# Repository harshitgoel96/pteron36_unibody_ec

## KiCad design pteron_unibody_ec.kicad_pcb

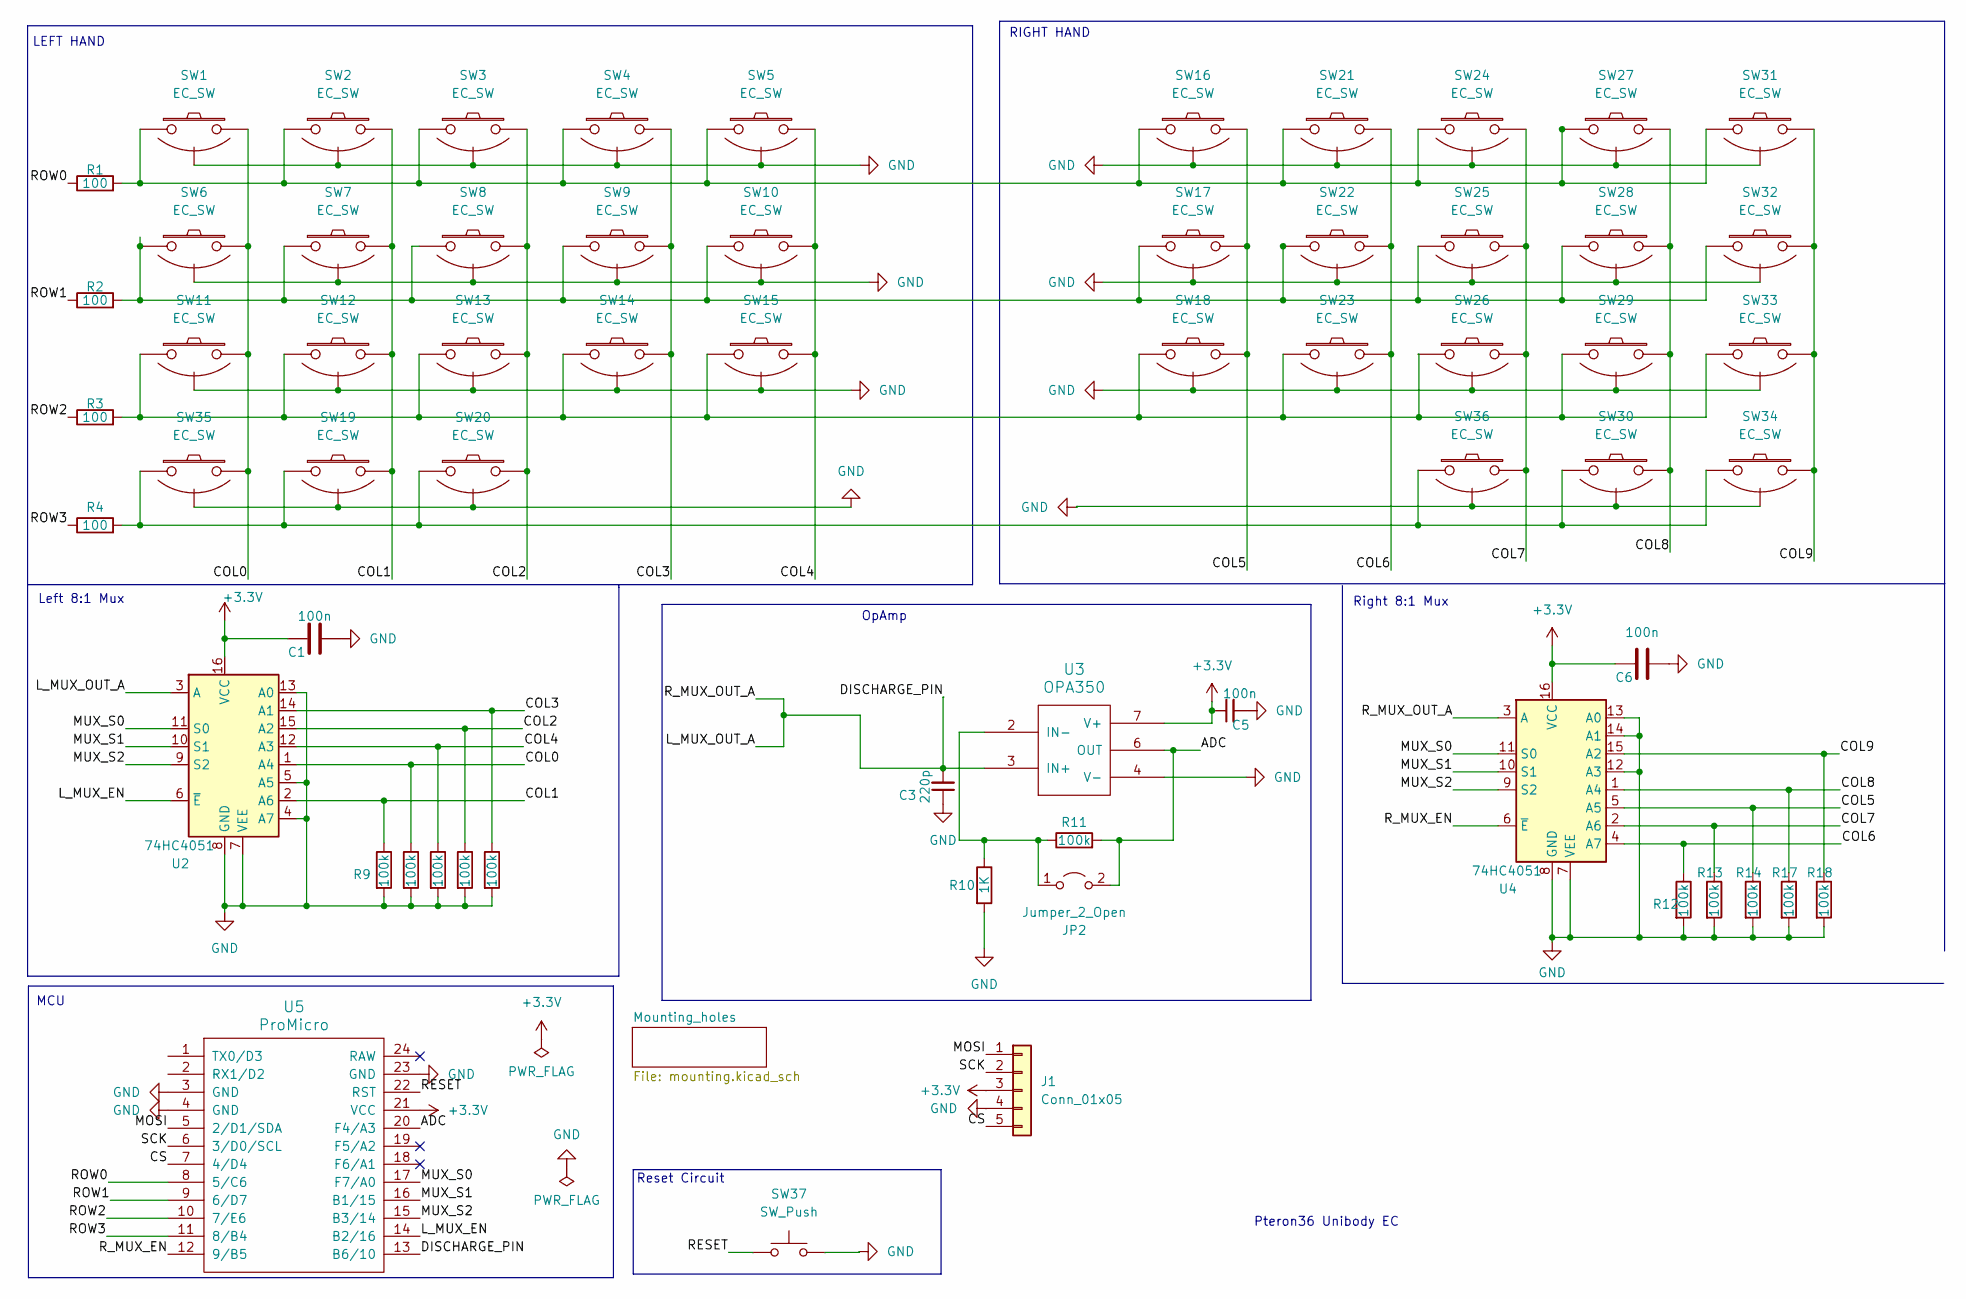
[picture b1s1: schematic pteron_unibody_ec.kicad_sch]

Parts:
C1, C5, C6: 100n; C_0805_2012Metric_Pad1.18x1.45mm_HandSolder
C3: 220p; C_0805_2012Metric_Pad1.18x1.45mm_HandSolder
J1: Conn_01x05; nice_view
JP2: Jumper_2_Open; R_0805_2012Metric_Pad1.20x1.40mm_HandSolder
R1, R2, R3, R4: 100; R_0805_2012Metric_Pad1.20x1.40mm_HandSolder
R5, R6, R7, R8, R9, R11, R12, R13, R14, R17, R18: 100k; R_0805_2012Metric_Pad1.20x1.40mm_HandSolder
R10: 1K; R_0805_2012Metric_Pad1.20x1.40mm_HandSolder
SW1, SW2, SW3, SW4, SW5, SW6, SW7, SW8, SW9, SW10, SW11, SW12, SW13, SW14, SW15, SW16, SW17, SW18, SW21, SW22, SW23, SW24, SW25, SW26, SW27, SW28, SW29, SW31, SW32, SW33: EC_SW; ecs_pad_1U_no_ring_90_fix
SW19, SW20, SW30, SW34, SW35, SW36: EC_SW; ecs_pad_1U_no_ring_90deg
SW37: SW_Push; SolderJumper-2_P1.3mm_Open_Pad1.0x1.5mm
U2, U4: 74HC4051; SOIC-16_3.9x9.9mm_P1.27mm
U3: OPA350; SOIC-8_3.9x4.9mm_P1.27mm
U5: ProMicro; ArduinoProMicro

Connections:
+3.3V: C1.1, C5.1, C6.1, J1.3, U2.16 (VCC), U3.7 (V+), U4.16 (VCC), U5.21 (VCC)
/ADC: JP2.2 (B), R11.2, U3.6 (OUT), U5.20 (F4/A3)
/COL0: R8.1, SW1.2, SW6.2, SW11.2, SW35.2, U2.1 (A4)
/COL1: R9.1, SW2.2, SW7.2, SW12.2, SW19.2, U2.2 (A6)
/COL2: R6.1, SW3.2, SW8.2, SW13.2, SW20.2, U2.15 (A2)
/COL3: R5.1, SW4.2, SW9.2, SW14.2, U2.14 (A1)
/COL4: R7.1, SW5.2, SW10.2, SW15.2, U2.12 (A3)
/COL5: R14.1, SW16.2, SW17.2, SW18.2, U4.5 (A5)
/COL6: R12.1, SW21.2, SW22.2, SW23.2, U4.4 (A7)
/COL7: R13.1, SW24.2, SW25.2, SW26.2, SW36.2, U4.2 (A6)
/COL8: R17.1, SW27.2, SW28.2, SW29.2, SW30.2, U4.1 (A4)
/COL9: R18.1, SW31.2, SW32.2, SW33.2, SW34.2, U4.15 (A2)
/CS: J1.5, U5.7 (4/D4)
/DISCHARGE_PIN: C3.2, U2.3 (A), U3.3 (IN+), U4.3 (A), U5.13 (B6/10)
/L_MUX_EN: U2.6 (~E), U5.14 (B2/16)
/MOSI: J1.1, U5.5 (2/D1/SDA)
/MUX_S0: U2.11 (S0), U4.11 (S0), U5.17 (F7/A0)
/MUX_S1: U2.10 (S1), U4.10 (S1), U5.16 (B1/15)
/MUX_S2: U2.9 (S2), U4.9 (S2), U5.15 (B3/14)
/RESET: SW37.1, U5.22 (RST)
/ROW0: R1.1, U5.8 (5/C6)
/ROW1: R2.1, U5.9 (6/D7)
/ROW2: R3.1, U5.10 (7/E6)
/ROW3: R4.1, U5.11 (8/B4)
/R_MUX_EN: U4.6 (~E), U5.12 (9/B5)
/SCK: J1.2, U5.6 (3/D0/SCL)
GND: C1.2, C3.1, C5.2, C6.2, J1.4, R5.2, R6.2, R7.2, R8.2, R9.2, R10.2, R12.2, R13.2, R14.2, R17.2, R18.2, SW1.3 (SG), SW2.3 (SG), SW3.3 (SG), SW4.3 (SG), SW5.3 (SG), SW6.3 (SG), SW7.3 (SG), SW8.3 (SG), SW9.3 (SG), SW10.3 (SG), SW11.3 (SG), SW12.3 (SG), SW13.3 (SG), SW14.3 (SG), SW15.3 (SG), SW16.3 (SG), SW17.3 (SG), SW18.3 (SG), SW19.3 (SG), SW20.3 (SG), SW21.3 (SG), SW22.3 (SG), SW23.3 (SG), SW24.3 (SG), SW25.3 (SG), SW26.3 (SG), SW27.3 (SG), SW28.3 (SG), SW29.3 (SG), SW30.3 (SG), SW31.3 (SG), SW32.3 (SG), SW33.3 (SG), SW34.3 (SG), SW35.3 (SG), SW36.3 (SG), SW37.2, U2.4 (A7), U2.5 (A5), U2.7 (VEE), U2.8 (GND), U2.13 (A0), U3.4 (V-), U4.7 (VEE), U4.8 (GND), U4.12 (A3), U4.13 (A0), U4.14 (A1), U5.3 (GND), U5.4 (GND), U5.23 (GND)
unnamed: JP2.1 (A), R10.1, R11.1, U3.2 (IN-)
unnamed: R1.2, SW1.1, SW2.1, SW3.1, SW4.1, SW5.1, SW16.1, SW21.1, SW24.1, SW27.1, SW31.1
unnamed: R2.2, SW6.1, SW7.1, SW8.1, SW9.1, SW10.1, SW17.1, SW22.1, SW25.1, SW28.1, SW32.1
unnamed: R3.2, SW11.1, SW12.1, SW13.1, SW14.1, SW15.1, SW18.1, SW23.1, SW26.1, SW29.1, SW33.1
unnamed: R4.2, SW19.1, SW20.1, SW30.1, SW34.1, SW35.1, SW36.1

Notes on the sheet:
MCU
RIGHT HAND
Right 8:1 Mux
Pteron36 Unibody EC
Reset Circuit
OpAmp
Left 8:1 Mux
LEFT HAND

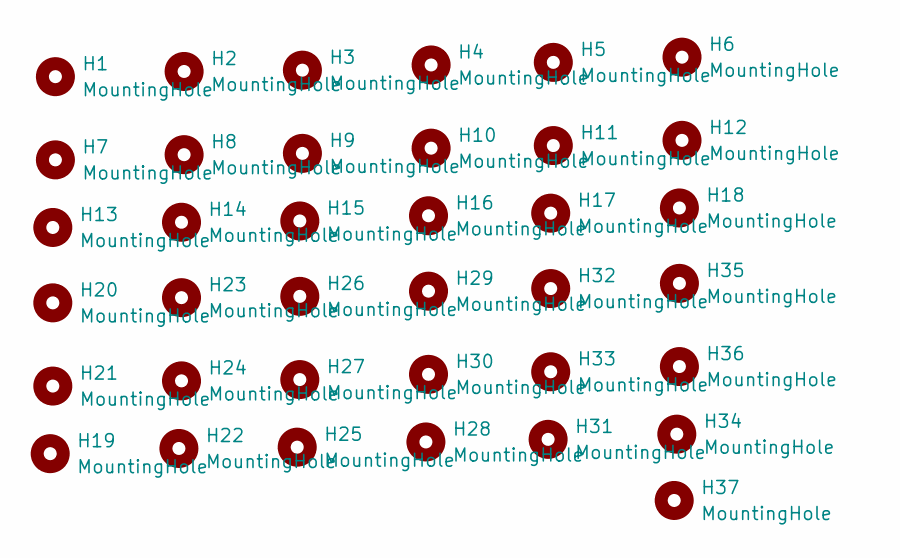
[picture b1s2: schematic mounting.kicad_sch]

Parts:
H1, H2, H3, H4, H5, H6, H7, H8, H9, H10, H11, H12, H13, H14, H15, H16, H17, H18, H19, H20, H21, H22, H23, H24, H25, H26, H27, H28, H29, H30, H31, H32, H33, H34, H35, H36, H37: MountingHole; MountingHole_2.2mm_M2_DIN965

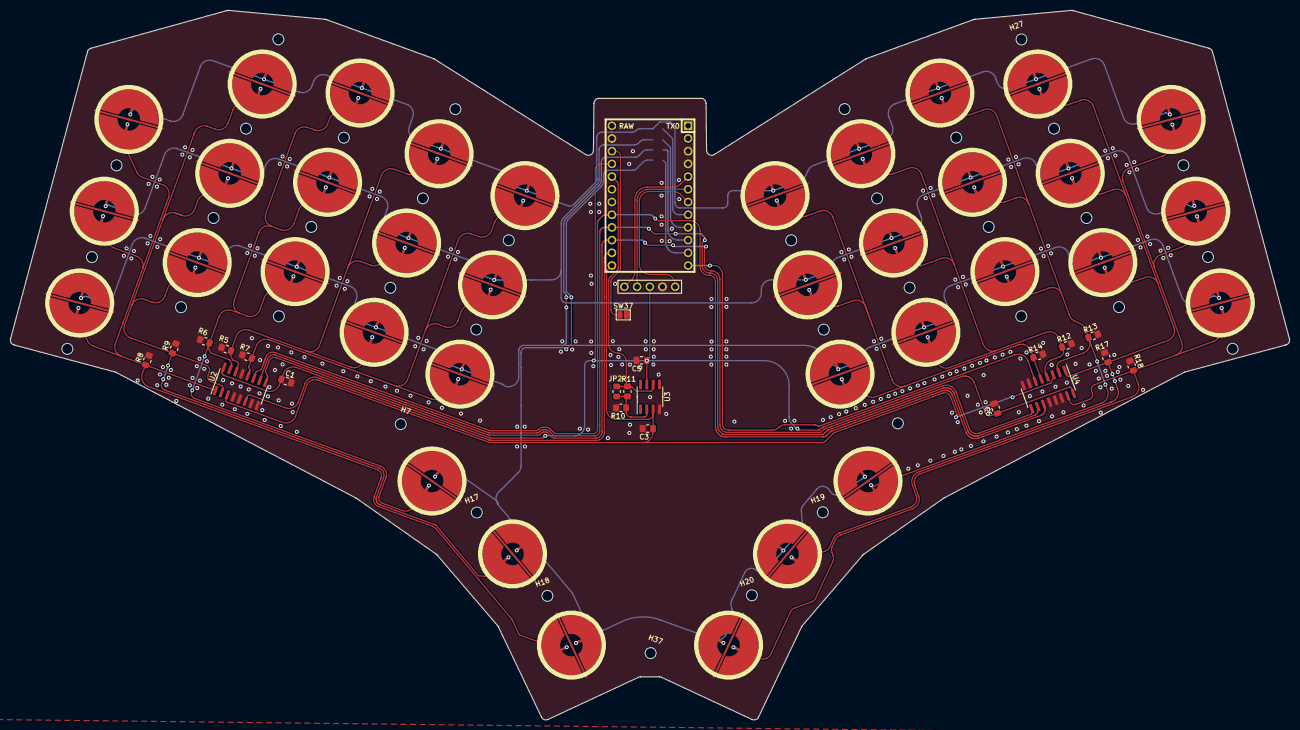
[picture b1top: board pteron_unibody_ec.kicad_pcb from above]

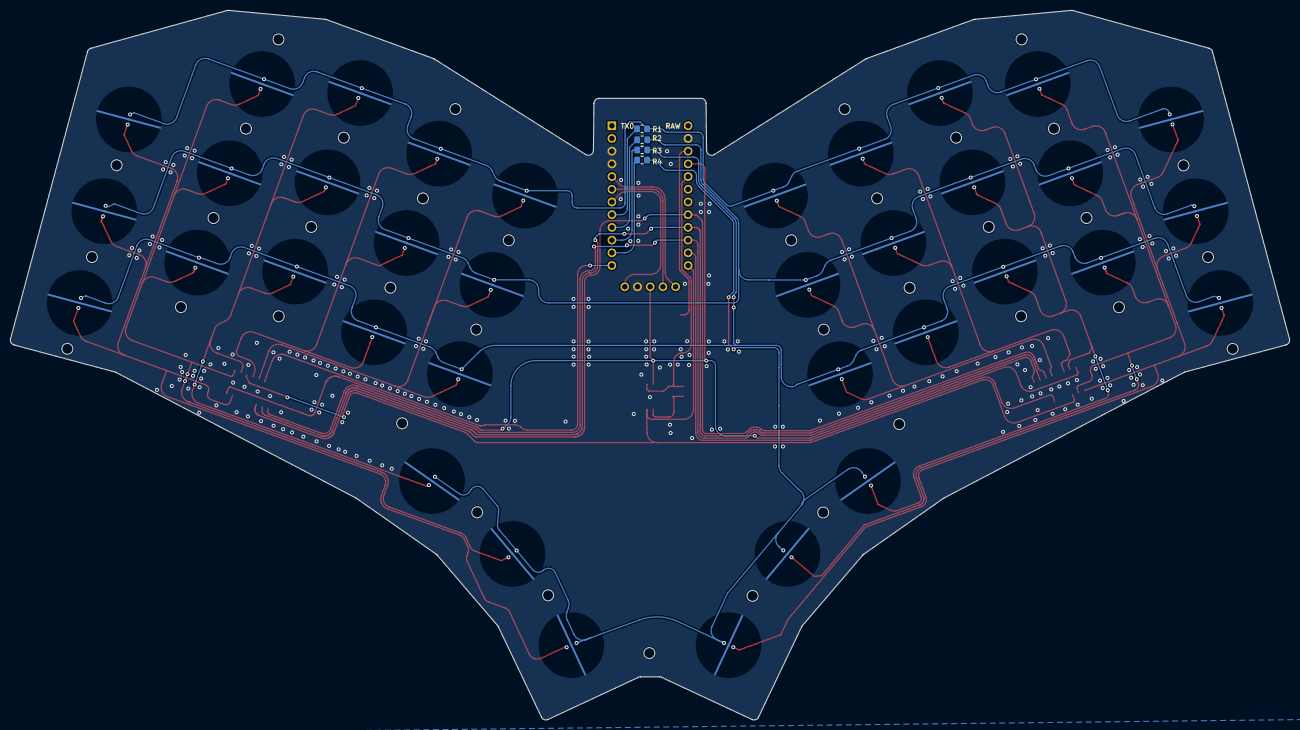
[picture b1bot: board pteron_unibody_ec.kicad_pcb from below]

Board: 2 copper layers, 255.8 x 141.9 mm, 100 parts (5 on the bottom side), 32 nets.

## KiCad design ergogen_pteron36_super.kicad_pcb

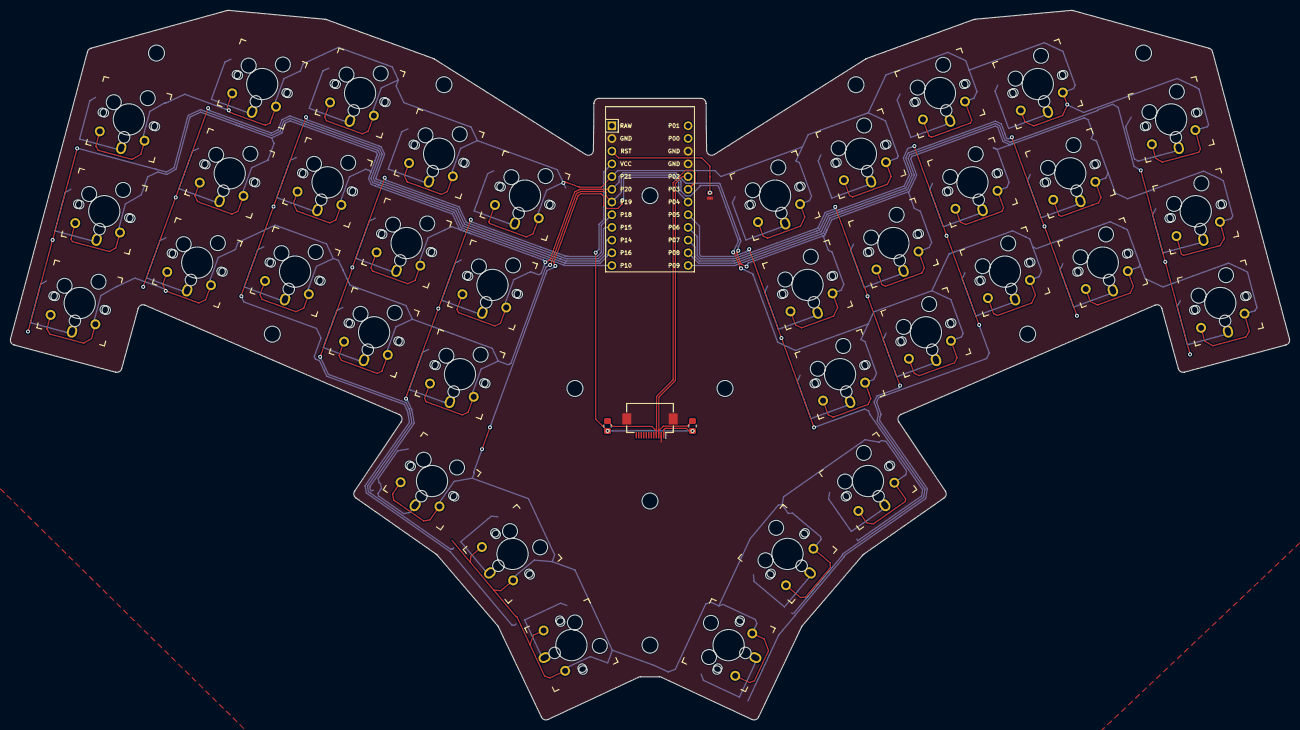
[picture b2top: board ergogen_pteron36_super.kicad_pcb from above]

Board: 2 copper layers, 255.8 x 141.9 mm, 50 parts (0 on the bottom side), 19 nets.

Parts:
FC1: Hirose_FH12-12S-0.5SH_1x12-1MP_P0.50mm_Horizontal
H1, H2, H3, H4, H5, H6, H7, H8: MountingHole_3.2mm_M3
J1, J2: Jumper
MCU1: ProMicro
R1, R2: R_0805; R_0805_2012Metric_Pad1.20x1.40mm_HandSolder
key1, key2, key3, key4, key5, key6, key7, key8, key9, key10, key11, key12, key13, key14, key15, key16, key17, key18, key19, key20, key21, key22, key23, key24, key25, key26, key27, key28, key29, key30, key31, key32, key33, key34, key35, key36: Kailh_socket_MX_LP

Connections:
C1: MCU1.12, key1.2, key2.2, key3.2
C2: MCU1.11, key4.2, key5.2, key6.2
C3: MCU1.10, key7.2, key8.2, key9.2, key18.2
C4: MCU1.9, key10.2, key11.2, key12.2, key17.2
C5: MCU1.8, key13.2, key14.2, key15.2, key16.2
C6: MCU1.20, key31.2, key32.2, key33.2, key34.2
C7: MCU1.21, key28.2, key29.2, key30.2, key35.2
C8: MCU1.22, key25.2, key26.2, key27.2, key36.2
C9: MCU1.23, key22.2, key23.2, key24.2
C10: MCU1.24, key19.2, key20.2, key21.2
GND: FC1.2, FC1.MP, J1.2, J2.2, MCU1.2, MCU1.15, MCU1.16
R1: MCU1.5, key3.1, key6.1, key9.1, key12.1, key15.1, key21.1, key24.1, key27.1, key30.1, key33.1
R2: MCU1.6, key2.1, key5.1, key8.1, key11.1, key14.1, key20.1, key23.1, key26.1, key29.1, key32.1
R3: MCU1.7, key1.1, key4.1, key7.1, key10.1, key13.1, key19.1, key22.1, key25.1, key28.1, key31.1
R4: MCU1.19, key16.1, key17.1, key18.1, key34.1, key35.1, key36.1
RST: J1.1, J2.1, MCU1.3
SCL: FC1.4, MCU1.18, R2.2
SDA: FC1.3, MCU1.17, R1.2
VCC: FC1.1, MCU1.4, R1.1, R2.1

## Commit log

2023-09-24 inital commit
2023-09-24 updated pcb with correct opamp schema and single source of mux sel
2023-09-25 updated trace with fillet
2023-09-25 updated traces and 3d footprints
2023-09-25 final version
